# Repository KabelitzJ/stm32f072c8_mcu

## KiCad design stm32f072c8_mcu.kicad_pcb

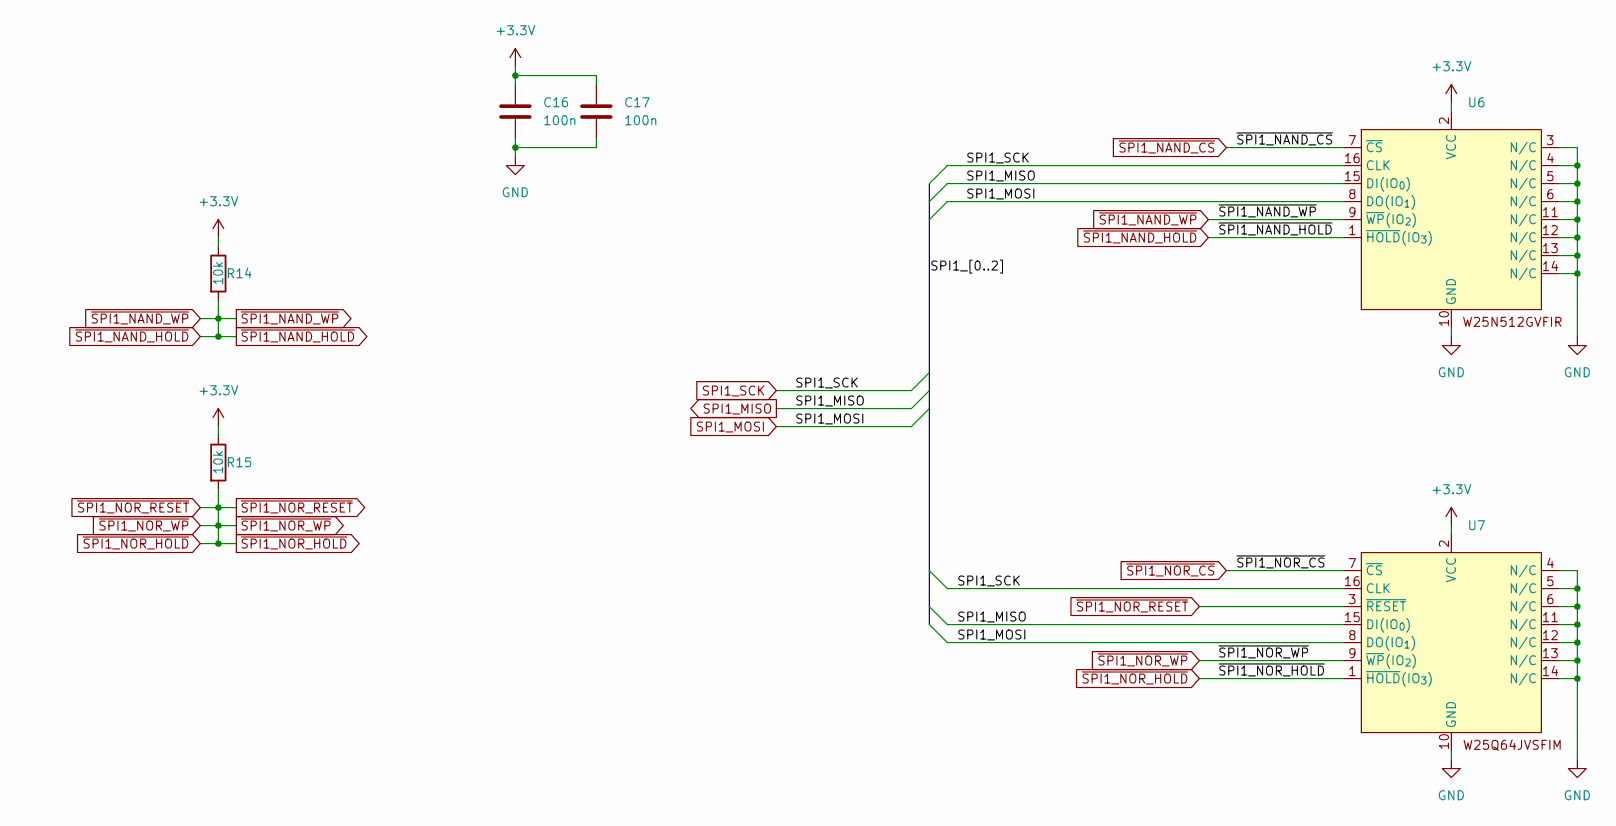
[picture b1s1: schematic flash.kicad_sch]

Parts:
C16, C17: 100n; C_0603_1608Metric
R14, R15: 10k; R_0603_1608Metric
U6, U7: SOIC-16W_7.5x10.3mm_P1.27mm

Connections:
+3.3V: C16.1, C17.1, R14.1, R15.1, U6.2 (VCC), U7.2 (VCC); also elsewhere on the board
GND: C16.2, C17.2, U6.3 (N/C), U6.4 (N/C), U6.5 (N/C), U6.6 (N/C), U6.10 (GND), U6.11 (N/C), U6.12 (N/C), U6.13 (N/C), U6.14 (N/C), U7.4 (N/C), U7.5 (N/C), U7.6 (N/C), U7.10 (GND), U7.11 (N/C), U7.12 (N/C), U7.13 (N/C), U7.14 (N/C); also elsewhere on the board
SPI1_MISO: U6.15 (DI(IO_{0})), U7.15 (DI(IO_{0})); also elsewhere on the board
SPI1_MOSI: U6.8 (DO(IO_{1})), U7.8 (DO(IO_{1})); also elsewhere on the board
SPI1_SCK: U6.16 (CLK), U7.16 (CLK); also elsewhere on the board
~SPI1_NAND_CS: U6.7 (~CS); also elsewhere on the board
~SPI1_NAND_HOLD: R14.2, U6.1 (~HOLD(IO_{3})), U6.9 (~WP(IO_{2}))
~SPI1_NOR_CS: U7.7 (~CS); also elsewhere on the board
~SPI1_NOR_HOLD: R15.2, U7.1 (~HOLD(IO_{3})), U7.3 (~RESET), U7.9 (~WP(IO_{2}))

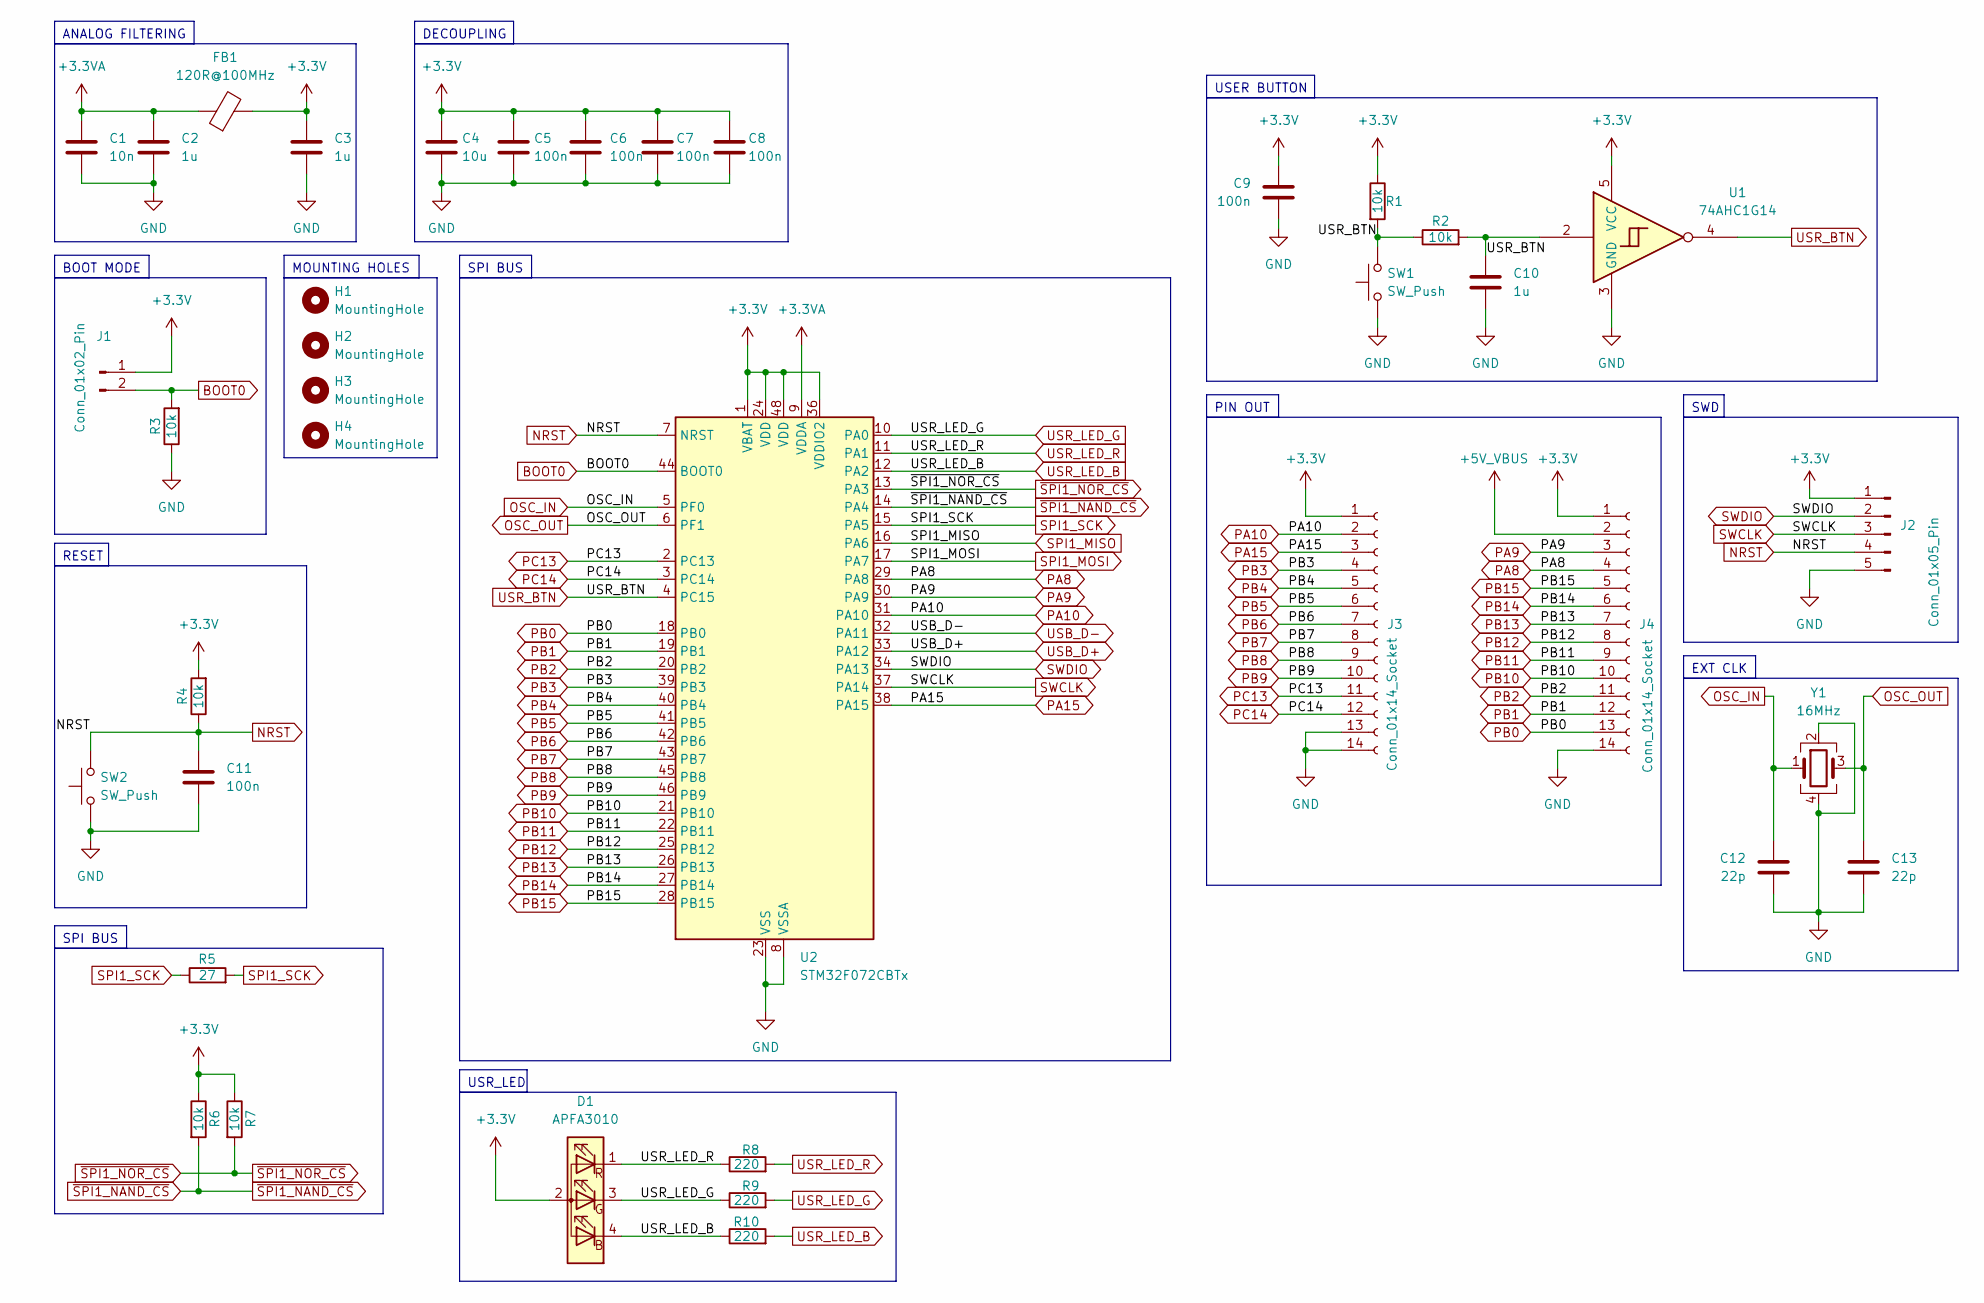
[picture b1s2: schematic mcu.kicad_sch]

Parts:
C1: 10n; C_0603_1608Metric
C2, C3, C10: 1u; C_0603_1608Metric
C4: 10u; C_0603_1608Metric
C5, C6, C7, C8, C9, C11: 100n; C_0603_1608Metric
C12, C13: 22p; C_0603_1608Metric
D1: APFA3010; 2.8x3.5_LED_RGB
FB1: 120R@100MHz; R_0603_1608Metric
H1, H2, H3, H4: MountingHole; MountingHole_2.2mm_M2_DIN965
J1: Conn_01x02_Pin; PinHeader_1x02_P2.54mm_Vertical
J2: Conn_01x05_Pin; PinHeader_1x05_P2.54mm_Vertical
J3, J4: Conn_01x14_Socket; PinSocket_1x14_P2.54mm_Vertical
R1, R2, R3, R4, R6, R7: 10k; R_0603_1608Metric
R5: 27; R_0603_1608Metric
R8, R9, R10: 220; R_0603_1608Metric
SW1, SW2: SW_Push; SW_Push_SPST_NO_Alps_SKRK
U1: 74AHC1G14; SOT-353_SC-70-5_Handsoldering
U2: STM32F072CBTx; LQFP-48_7x7mm_P0.5mm
Y1: 16MHz; 3225_smd_crystal

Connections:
+3.3V: C3.1, C4.1, C5.1, C6.1, C7.1, C8.1, C9.1, D1.2 (A), FB1.2, J1.1, J2.1, J3.1, J4.1, R1.1, R4.2, R6.1, R7.1, U1.5 (VCC), U2.1 (VBAT), U2.24 (VDD), U2.36 (VDDIO2), U2.48 (VDD); also elsewhere on the board
+3.3VA: C1.1, C2.1, FB1.1, U2.9 (VDDA)
+5V_VBUS: J4.2; also elsewhere on the board
BOOT0: J1.2, R3.2, U2.44 (BOOT0)
GND: C1.2, C2.2, C3.2, C4.2, C5.2, C6.2, C7.2, C8.2, C9.2, C10.2, C11.2, C12.2, C13.2, J2.5, J3.13, J3.14, J4.14, R3.1, SW1.1, SW2.1, U1.3 (GND), U2.8 (VSSA), U2.23 (VSS), U2.35 (VSS), U2.47 (VSS), Y1.2, Y1.4; also elsewhere on the board
NRST: C11.1, J2.4, R4.1, SW2.2, U2.7 (NRST)
OSC_IN: C12.1, U2.5 (PF0), Y1.1
OSC_OUT: C13.1, U2.6 (PF1), Y1.3
PA8: J4.4, U2.29 (PA8)
PA9: J4.3, U2.30 (PA9)
PA10: J3.2, U2.31 (PA10)
PA15: J3.3, U2.38 (PA15)
PB0: J4.13, U2.18 (PB0)
PB1: J4.12, U2.19 (PB1)
PB2: J4.11, U2.20 (PB2)
PB3: J3.4, U2.39 (PB3)
PB4: J3.5, U2.40 (PB4)
PB5: J3.6, U2.41 (PB5)
PB6: J3.7, U2.42 (PB6)
PB7: J3.8, U2.43 (PB7)
PB8: J3.9, U2.45 (PB8)
PB9: J3.10, U2.46 (PB9)
PB10: J4.10, U2.21 (PB10)
PB11: J4.9, U2.22 (PB11)
PB12: J4.8, U2.25 (PB12)
PB13: J4.7, U2.26 (PB13)
PB14: J4.6, U2.27 (PB14)
PB15: J4.5, U2.28 (PB15)
PC13: J3.11, U2.2 (PC13)
PC14: J3.12, U2.3 (PC14)
SPI1_MISO: U2.16 (PA6); also elsewhere on the board
SPI1_MOSI: U2.17 (PA7); also elsewhere on the board
SPI1_SCK: R5.1, R5.2, U2.15 (PA5); also elsewhere on the board
SWCLK: J2.3, U2.37 (PA14)
SWDIO: J2.2, U2.34 (PA13)
USB_D+: U2.33 (PA12); also elsewhere on the board
USB_D-: U2.32 (PA11); also elsewhere on the board
USR_BTN: C10.1, R1.2, R2.1, R2.2, SW1.2, U1.2, U1.4, U2.4 (PC15)
USR_LED_B: D1.4 (B), R10.1, R10.2, U2.12 (PA2)
USR_LED_G: D1.3 (G), R9.1, R9.2, U2.10 (PA0)
USR_LED_R: D1.1 (R), R8.1, R8.2, U2.11 (PA1)
~SPI1_NAND_CS: R6.2, U2.14 (PA4); also elsewhere on the board
~SPI1_NOR_CS: R7.2, U2.13 (PA3); also elsewhere on the board

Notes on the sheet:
EXT CLK
USER BUTTON
SPI BUS
ANALOG FILTERING
BOOT MODE
PIN OUT
RESET
DECOUPLING
USR_LED
SWD
MOUNTING HOLES

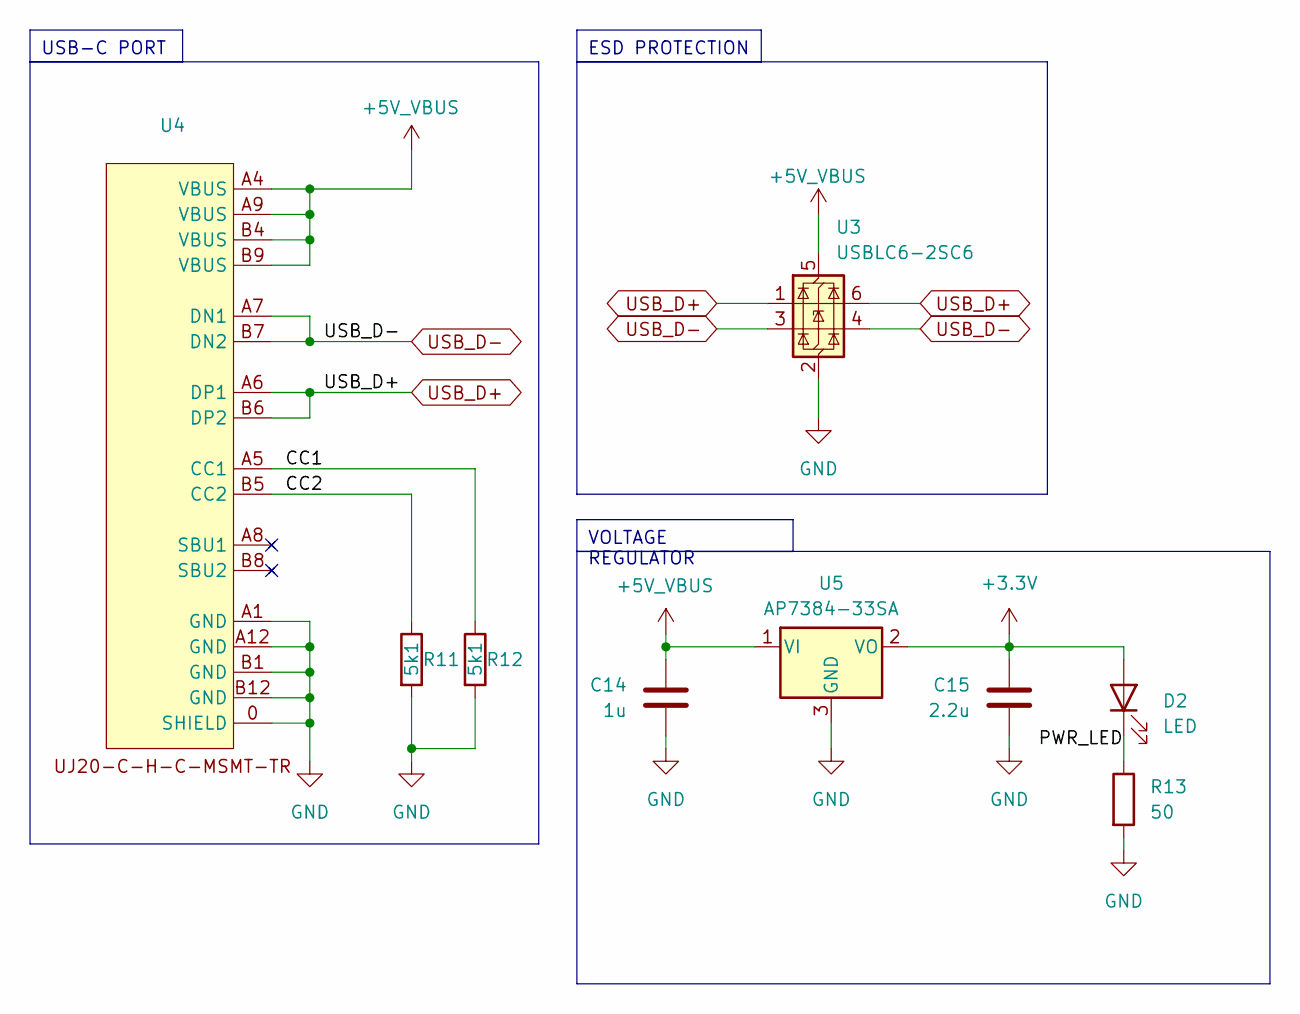
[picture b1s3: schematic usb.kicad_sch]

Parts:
C14: 1u; C_0603_1608Metric
C15: 2.2u; C_0603_1608Metric
D2: LED; LED_PLCC-2_3x2mm_KA
R11, R12: 5k1; R_0603_1608Metric
R13: 50; R_0603_1608Metric
U3: USBLC6-2SC6; SOT-23-6
U4: 640-USB4215-03-A
U5: AP7384-33SA; SOT-23

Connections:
+3.3V: C15.1, D2.2 (A), U5.2 (VO); also elsewhere on the board
+5V_VBUS: C14.1, U3.5 (VBUS), U4.A4 (VBUS), U4.A9 (VBUS), U4.B4 (VBUS), U4.B9 (VBUS), U5.1 (VI); also elsewhere on the board
/USB/CC1: R12.1, U4.A5 (CC1)
/USB/CC2: R11.1, U4.B5 (CC2)
/USB/PWR_LED: D2.1 (K), R13.1
GND: C14.2, C15.2, R11.2, R12.2, R13.2, U3.2 (GND), U4.0 (SHIELD), U4.A1 (GND), U4.A12 (GND), U4.B1 (GND), U4.B12 (GND), U5.3 (GND); also elsewhere on the board
USB_D+: U3.1 (I/O1), U3.6 (I/O1), U4.A6 (DP1), U4.B6 (DP2); also elsewhere on the board
USB_D-: U3.3 (I/O2), U3.4 (I/O2), U4.A7 (DN1), U4.B7 (DN2); also elsewhere on the board

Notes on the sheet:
ESD PROTECTION
VOLTAGE REGULATOR
USB-C PORT

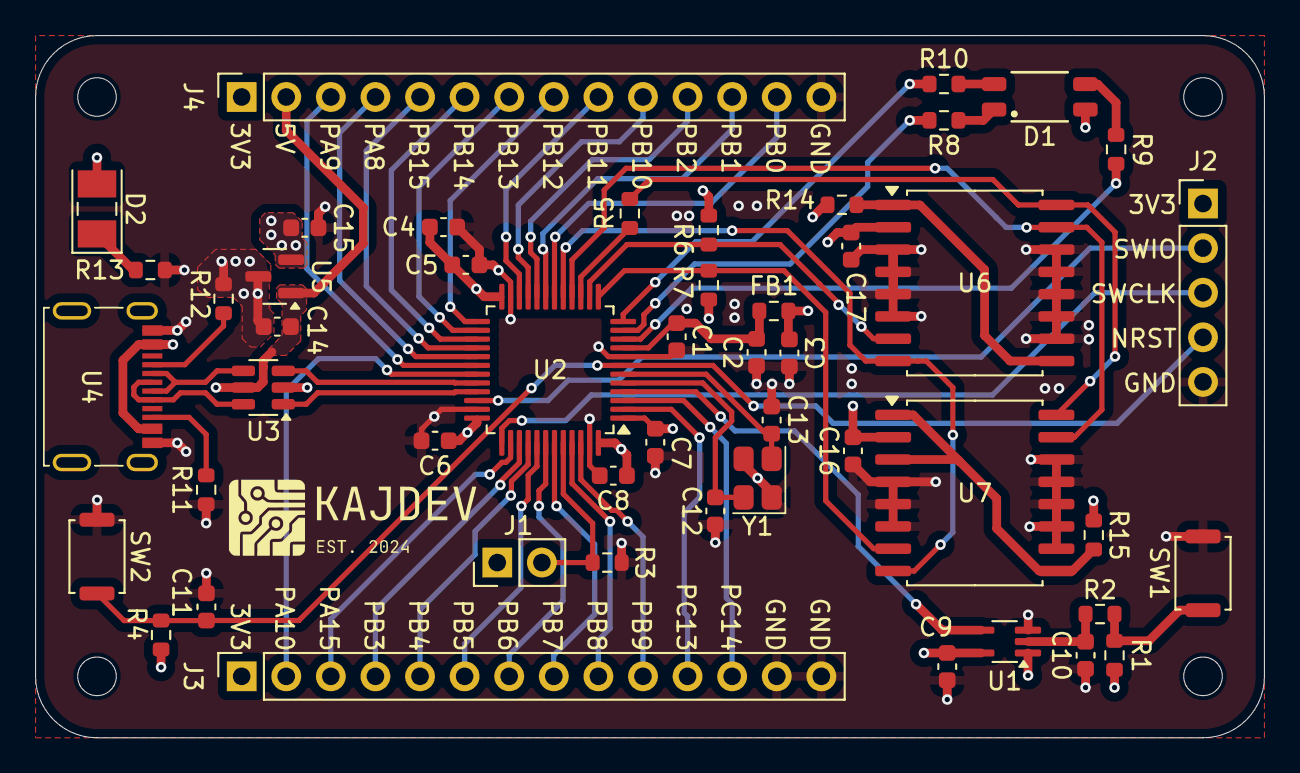
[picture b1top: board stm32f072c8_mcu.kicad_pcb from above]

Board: 4 copper layers, 70.0 x 40.0 mm, 53 parts (0 on the bottom side), 48 nets.

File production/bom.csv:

Designator,Footprint,Quantity,Value,LCSC Part #
C1,0603,1,10n,
"C10, C14, C2, C3",0603,4,1u,
"C11, C16, C17, C5, C6, C7, C8, C9",0603,8,100n,
"C12, C13",0603,2,22p,
C15,0603,1,2.2u,
C4,0603,1,10u,
D1,2.8x3.5_LED_RGB,1,APFA3010,
D2,LED_PLCC-2_3x2mm_KA,1,LED,
FB1,0603,1,120R@100MHz,
J1,PinHeader_1x02_P2.54mm_Vertical,1,Conn_01x02_Pin,
J2,PinHeader_1x05_P2.54mm_Vertical,1,Conn_01x05_Pin,
"J3, J4",PinSocket_1x14_P2.54mm_Vertical,2,Conn_01x14_Socket,
"R1, R15, R2, R3, R4, R6, R7",0603,7,10k,
"R10, R8, R9",0603,3,220,
"R11, R12",0603,2,5k1,
R13,0603,1,50,
R5,0603,1,27,
"SW1, SW2",SW_Push_SPST_NO_Alps_SKRK,2,SW_Push,
U1,SOT-353_SC-70-5_Handsoldering,1,74AHC1G14,
U2,LQFP-48_7x7mm_P0.5mm,1,STM32F072CBTx,
U3,SOT-23-6,1,USBLC6-2SC6,
U4,640-USB4215-03-A,1,~,
U5,SOT-23,1,AP7384-33SA,
"U6, U7",SOIC-16W_7.5x10.3mm_P1.27mm,2,~,
Y1,3225_smd_crystal,1,16MHz,

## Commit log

2024-11-26 fsdfsdf
2024-11-28 dasdsad
2024-12-04 sdsdfsd
